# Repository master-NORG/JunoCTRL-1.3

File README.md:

# JunoCTRL-1.3
Alpha Juno Hardware Controller

This is the repository for the JunoCTRL Alpha Juno controller from MIDI , which was released in 2015 and slowly upgraded and developed over the years until 2020.  You may use these files if you want to make your own JunoCTRL, modify your unit or would like to make a batch to bring down the price of components.  Be aware that I wrote the firmware 6 years ago when I knew almost nothing about C++ programming, it's awful to look at.  However, it works well, performs well and is bug-free.

I am not going to spend the time to document this project better, not that I don't want to, I just don't have the time. Although MIDI Club is no longer a thing, you can still reach us for questions about this project anytime at midiclub604@gmail.com

Note: there are two pcb boards, the main board and the smaller rear board for the switches, power and midi sockets. If you are making a JunoCTRL with the DIY acrylic case then you only need the main board and not the rear PCB.

Happy hacking!

-Dylan

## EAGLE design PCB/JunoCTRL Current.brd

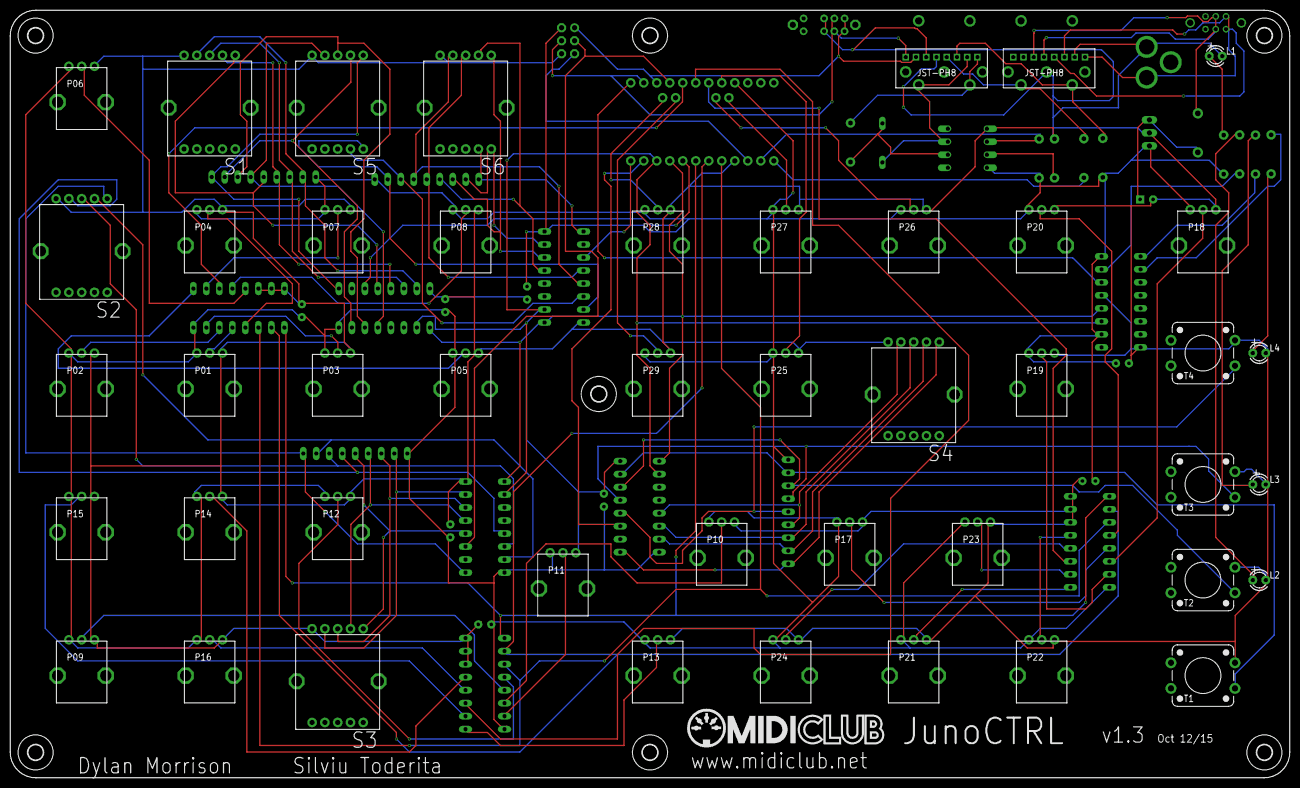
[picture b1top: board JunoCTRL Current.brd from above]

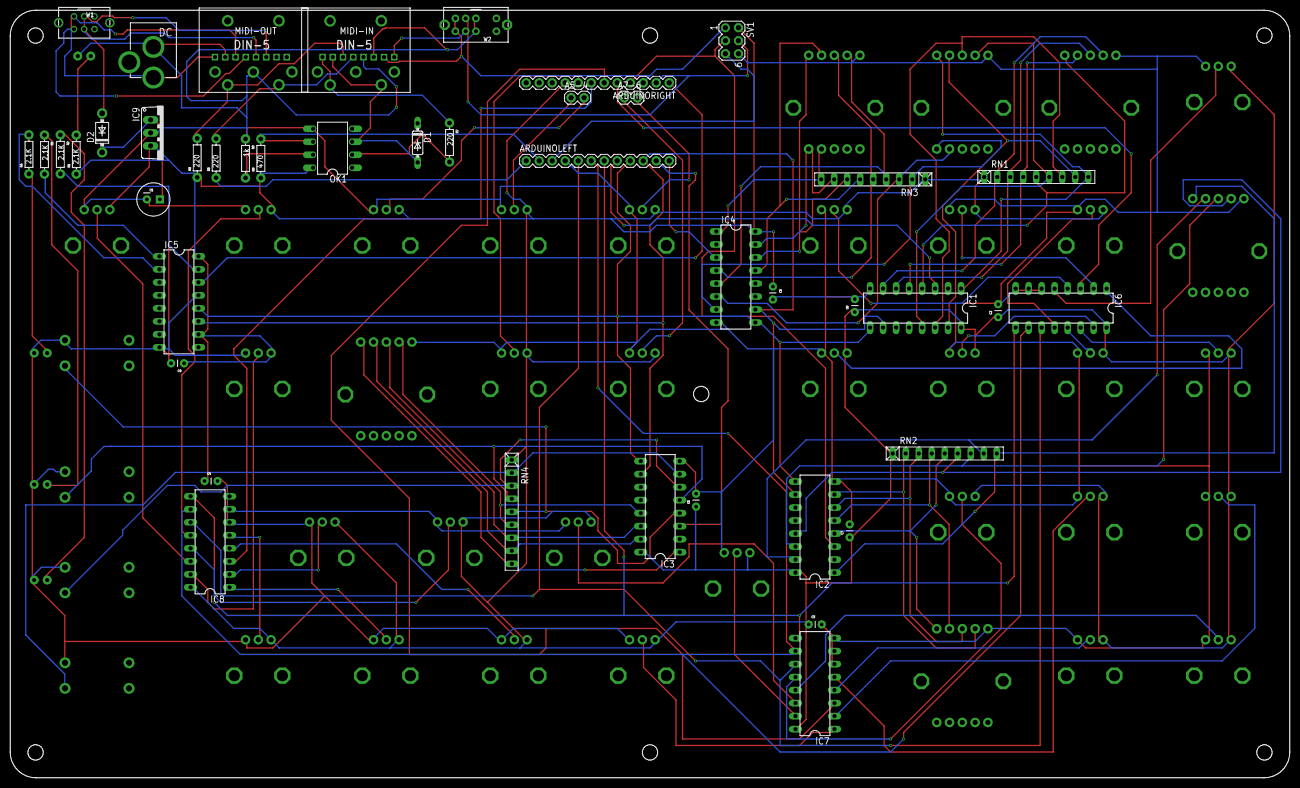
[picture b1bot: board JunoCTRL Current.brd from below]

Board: 2 copper layers, 249.9 x 149.9 mm, 96 parts (44 on the bottom side), 97 nets.

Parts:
A5-4, A7-6: 1X02
ARDUINOLEFT: 1X12
ARDUINORIGHT: 1X12
C1: 47uF; CPOL-RADIAL-100UF-25V
C2, C3, C4, C5, C6, C7, C8, C9: 0.1uF; CAP-PTH-SMALL
D1: 1N4148; DO35-7
D2: 1N4002; DO41-7
DC: POWER_JACKPTH; POWER_JACK_PTH
E$1, E$2: JSTCUSTOM_JST_PH8
IC1, IC2, IC3, IC4: 4021N; DIL16
IC5: 74HC595N; DIL16
IC6, IC7, IC8: 4051N; DIL16
IC9: 7805TV; TO220V
L1, L2, L3, L4: LED3MM
MIDI-IN: MIDI_CONN_FEMALE_SUPPORT; DIN_5_FEMALE_SUPPORT
MIDI-OUT: MIDI_CONN_FEMALE_SUPPORT; DIN_5_FEMALE_SUPPORT
OK1: 6N138; DIL08
P01, P02, P03, P04, P05, P06, P07, P08, P09, P10, P11, P12, P13, P14, P15, P16, P17, P18, P19, P20, P21, P22, P23, P24, P25, P26, P27, P28, P29: 10K; ALPS_POT
R1, R2, R3, R4: 2.1K; AXIAL-0.3
R5, R6, R7: 220; AXIAL-0.3
R8: 1k; AXIAL-0.3
R9: 470; AXIAL-0.3
RN1, RN2, RN3, RN4: 10k; RN-9
S1, S2, S3, S4: 4Pos; SRBV
S5, S6: 6Pos; SRBV
SV1: MA03-2
T1, T2, T3, T4: TACTILE-PTH-12MM
U$1, U$2, U$3, U$4, U$5, U$6, U$7: 3,0
W1: 0S-SPDT
W2: 0S-SP3T

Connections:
GND: ARDUINOLEFT.4, C1.2, C2.2, C3.2, C4.2, C5.2, C6.2, C7.2, C8.2, C9.2, DC.GND, E$1.P$5, E$1.P$6, E$2.P$2, IC1.8, IC2.8, IC3.8, IC4.8, IC5.8, IC5.13, IC6.6, IC6.7, IC6.8, IC7.6, IC7.7, IC7.8, IC8.6, IC8.7, IC8.8, IC9.2, L1.K, L2.K, L3.K, L4.K, MIDI-OUT.2, OK1.5, P01.P$1, P02.P$1, P03.P$1, P04.P$1, P05.P$1, P06.P$1, P07.P$1, P08.P$1, P09.P$1, P10.P$1, P11.P$1, P12.P$1, P13.P$1, P14.P$1, P15.P$1, P16.P$1, P17.P$1, P18.P$1, P19.P$1, P20.P$1, P21.P$1, P22.P$1, P23.P$1, P24.P$1, P25.P$1, P26.P$1, P27.P$1, P28.P$1, P29.P$1, R8.P$1, S1.1, S2.1, S3.1, S4.1, S5.1, S6.1, SV1.6, T1.3, T2.3, T3.3, T4.3, W2.PA2, W2.PA6
unnamed: IC7.4, P16.P$2
unnamed: IC6.4, P08.P$2
unnamed: IC6.2, P07.P$2
unnamed: IC6.5, P06.P$2
unnamed: IC6.1, P05.P$2
unnamed: IC6.12, P04.P$2
unnamed: IC6.15, P03.P$2
unnamed: IC6.14, P02.P$2
unnamed: IC6.13, P01.P$2
unnamed: IC7.2, P15.P$2
unnamed: IC7.5, P14.P$2
unnamed: IC7.1, P13.P$2
unnamed: IC7.12, P12.P$2
unnamed: IC7.15, P11.P$2
unnamed: IC7.14, P10.P$2
unnamed: IC7.13, P09.P$2
unnamed: IC8.4, P24.P$2
unnamed: IC8.2, P23.P$2
unnamed: IC8.5, P22.P$2
unnamed: IC8.1, P21.P$2
unnamed: IC8.12, P20.P$2
unnamed: IC8.15, P19.P$2
unnamed: IC8.14, P18.P$2
unnamed: IC8.13, P17.P$2
unnamed: ARDUINORIGHT.8, P25.P$2
unnamed: A5-4.2, P26.P$2
unnamed: A5-4.1, P27.P$2
unnamed: A7-6.2, P28.P$2
unnamed: A7-6.1, P29.P$2
unnamed: ARDUINOLEFT.5, IC6.11, IC7.11, IC8.11
unnamed: ARDUINOLEFT.6, IC6.10, IC7.10, IC8.10
unnamed: ARDUINOLEFT.7, IC6.9, IC7.9, IC8.9
unnamed: ARDUINORIGHT.5, IC6.3
unnamed: ARDUINORIGHT.6, IC7.3
unnamed: ARDUINORIGHT.7, IC8.3
unnamed: IC1.7, RN1.2, S1.2
unnamed: IC1.6, RN1.3, S1.3
unnamed: IC1.5, RN1.4, S1.4
unnamed: IC1.4, RN1.5, S1.5
unnamed: IC1.13, RN1.6, S5.2
unnamed: IC1.14, RN1.7, S5.3
unnamed: IC1.15, RN1.8, S5.4
unnamed: IC1.1, RN1.9, S5.5
unnamed: IC2.7, RN2.2, S3.2
unnamed: IC2.6, RN2.3, S3.3
unnamed: IC2.5, RN2.4, S3.4
unnamed: IC2.4, RN2.5, S3.5
unnamed: IC2.13, RN2.6, S2.2
unnamed: IC2.14, RN2.7, S2.3
unnamed: IC2.15, RN2.8, S2.4
unnamed: IC2.1, RN2.9, S2.5
unnamed: OK1.7, R8.P$2
unnamed: IC4.7, RN3.2, S5.6
unnamed: IC4.6, RN3.3, S5.7
unnamed: IC4.5, RN3.4, S6.2
unnamed: IC4.4, RN3.5, S6.3
unnamed: IC4.13, RN3.6, S6.4
unnamed: D2.A, E$2.P$5, E$2.P$6, W1.P1C, W1.P2C
unnamed: IC4.14, RN3.7, S6.5
unnamed: IC4.15, RN3.8, S6.6
unnamed: ARDUINORIGHT.3, E$1.P$7, SV1.1, W2.PA4, W2.PA8
unnamed: L1.A, R1.P$2
unnamed: ARDUINORIGHT.2, E$1.P$8, SV1.4, W2.PA3, W2.PA7
unnamed: IC5.15, R2.P$2
unnamed: L2.A, R2.P$1
unnamed: ARDUINORIGHT.1, IC5.14
unnamed: DC.PWR, E$2.P$1, E$2.P$3, E$2.P$4, W1.P1T2, W1.P2T2
unnamed: L3.A, R3.P$1
unnamed: ARDUINORIGHT.4, IC2.3, SV1.3
unnamed: E$1.P$1, MIDI-IN.4, R7.P$1
unnamed: D1.A, E$1.P$2, MIDI-IN.5, OK1.3
unnamed: C1.1, D2.C, IC9.1
unnamed: ARDUINOLEFT.2, OK1.6, R9.P$2
unnamed: E$1.P$4, MIDI-OUT.5, R5.P$2
unnamed: ARDUINOLEFT.1, R5.P$1
unnamed: E$1.P$3, MIDI-OUT.4, R6.P$2
unnamed: IC4.1, RN3.9, S6.7
unnamed: IC3.7, RN4.2, T1.1
unnamed: IC3.6, RN4.3, T2.1
unnamed: IC3.5, RN4.4, T3.1
unnamed: IC3.4, RN4.5, T4.1
unnamed: IC5.1, R3.P$2
unnamed: IC5.2, R4.P$2
unnamed: L4.A, R4.P$1
unnamed: D1.C, OK1.2, R7.P$2
unnamed: IC3.13, RN4.6, S4.2
unnamed: IC3.14, RN4.7, S4.3
unnamed: IC3.15, RN4.8, S4.4
unnamed: IC3.1, RN4.9, S4.5
unnamed: ARDUINOLEFT.3, SV1.5
SR5: ARDUINOLEFT.8, IC1.3
SR6: ARDUINOLEFT.9, IC1.9, IC2.9, IC3.9, IC4.9, IC5.12
SR7: ARDUINOLEFT.10, IC1.10, IC2.10, IC3.10, IC4.10, IC5.11
SR8: ARDUINOLEFT.11, IC3.3
SR9: ARDUINOLEFT.12, IC4.3
VCC: ARDUINORIGHT.9, C2.1, C3.1, C4.1, C5.1, C6.1, C7.1, C8.1, C9.1, IC1.16, IC2.16, IC3.16, IC4.16, IC5.10, IC5.16, IC6.16, IC7.16, IC8.16, IC9.3, OK1.8, P01.P$3, P02.P$3, P03.P$3, P04.P$3, P05.P$3, P06.P$3, P07.P$3, P08.P$3, P09.P$3, P10.P$3, P11.P$3, P12.P$3, P13.P$3, P14.P$3, P15.P$3, P16.P$3, P17.P$3, P18.P$3, P19.P$3, P20.P$3, P21.P$3, P22.P$3, P23.P$3, P24.P$3, P25.P$3, P26.P$3, P27.P$3, P28.P$3, P29.P$3, R1.P$1, R6.P$1, R9.P$1, RN1.1, RN2.1, RN3.1, RN4.1, SV1.2

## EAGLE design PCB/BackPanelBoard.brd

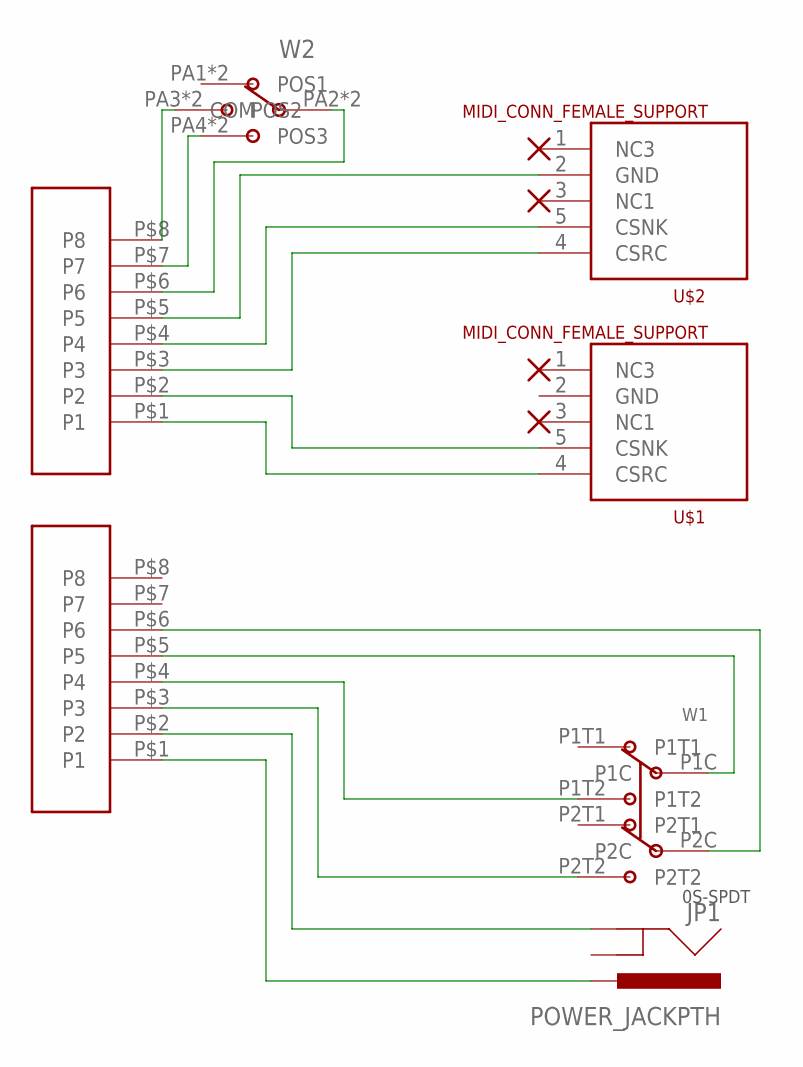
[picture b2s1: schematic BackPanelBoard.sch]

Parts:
JP1: POWER_JACKPTH; POWER_JACK_PTH
U$1, U$2: MIDI_CONN_FEMALE_SUPPORT; DIN_5_FEMALE_SUPPORT
U$3, U$4: JST_PH8THROUGH_HOLE; JST_PH8
W1: 0S-SPDT
W2: 0S-SP3T

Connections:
unnamed: U$1.4 (CSRC), U$3.P$1 (P1)
unnamed: U$1.5 (CSNK), U$3.P$2 (P2)
unnamed: U$2.4 (CSRC), U$3.P$3 (P3)
unnamed: U$2.5 (CSNK), U$3.P$4 (P4)
unnamed: U$2.2 (GND), U$3.P$5 (P5)
unnamed: JP1.PWR, U$4.P$1 (P1)
unnamed: JP1.GND, U$4.P$2 (P2)
unnamed: U$4.P$3 (P3), W1.P2T2
unnamed: U$4.P$4 (P4), W1.P1T2
unnamed: U$4.P$5 (P5), W1.P1C
unnamed: U$4.P$6 (P6), W1.P2C
unnamed: U$3.P$6 (P6), W2.PA2 (COM), W2.PA6 (COM)
unnamed: U$3.P$7 (P7), W2.PA4 (POS3), W2.PA8 (POS3)
unnamed: U$3.P$8 (P8), W2.PA3 (POS2), W2.PA7 (POS2)

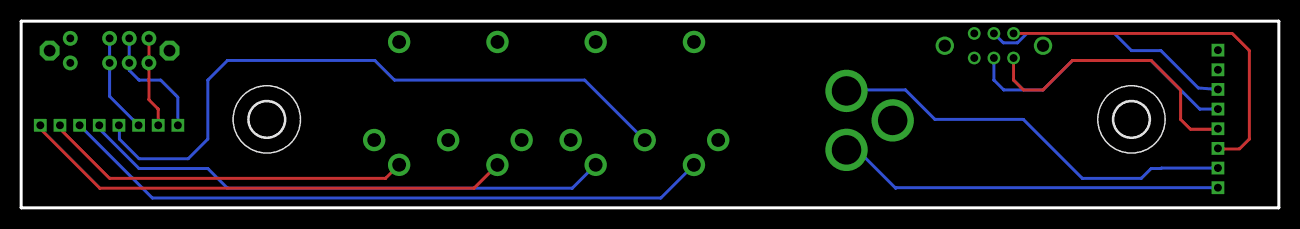
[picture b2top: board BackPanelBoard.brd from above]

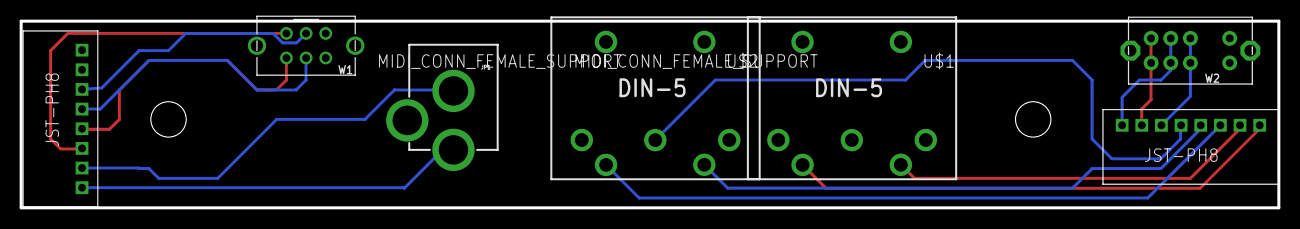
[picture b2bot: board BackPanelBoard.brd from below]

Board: 2 copper layers, 128.0 x 19.0 mm, 9 parts (7 on the bottom side), 14 nets.

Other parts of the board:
U$7, U$8: 3,6

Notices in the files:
parts and their libraries:
SparkFun-Connectors: Licensing: Creative Commons ShareAlike 4.0 International - https://creativecommons.org/licenses/by-sa/4.0
